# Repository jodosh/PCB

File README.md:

# PCB
eagleCAD files for PCB layouts

Each Directory is an entirly seperate project and should consist of at least 3 files

1)EagleCAD .brd file

2)EagleCAD .sch file

3)README

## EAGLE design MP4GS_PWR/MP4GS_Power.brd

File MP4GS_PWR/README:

This is a board for  the L7808AB 8V regulator input can be 10-35V.
This is used for converting from battery power to the Vin of a Mega2560

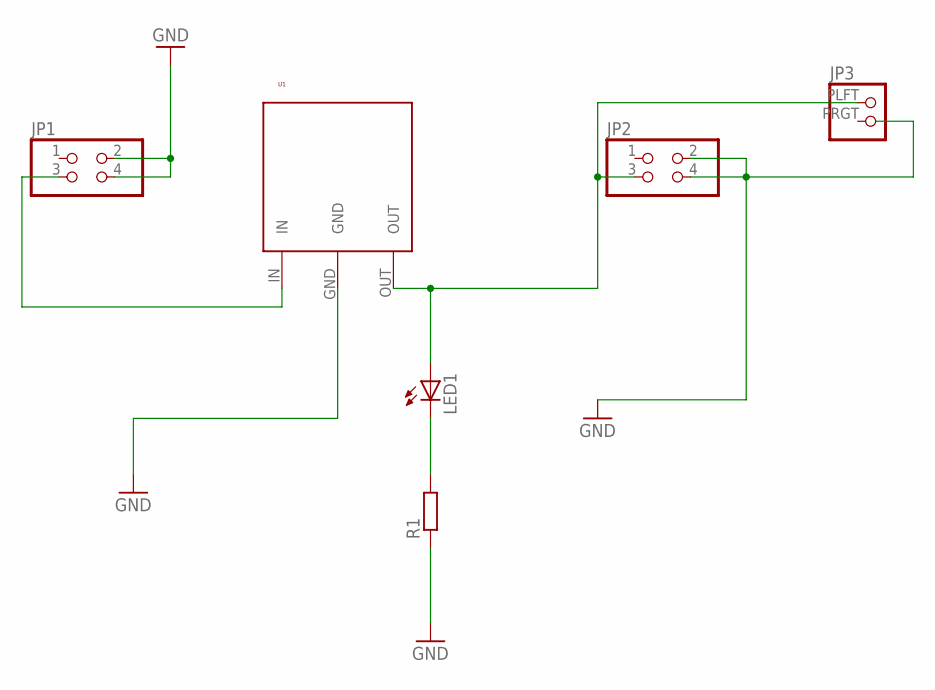
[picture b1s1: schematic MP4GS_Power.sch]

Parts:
JP1, JP2: PINHD-2X2; 2X02
JP3: PINHD-1X2; 1X02
LED1: LED5MM
R1: R-EU_0207/10; 0207/10
U1: L7808AB; L78-DDPAK

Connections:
GND: JP1.2, JP1.4, JP2.2, JP2.4, R1.1, U1.GND
unnamed: JP1.3, U1.IN
unnamed: JP2.3, JP3.PLFT (1), LED1.A, U1.OUT
unnamed: LED1.K (C), R1.2

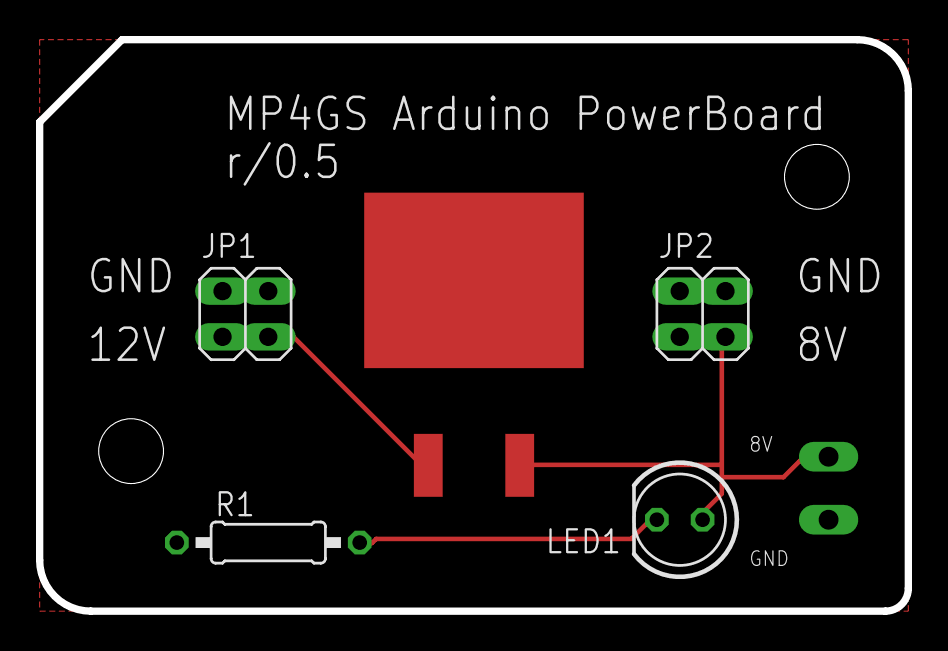
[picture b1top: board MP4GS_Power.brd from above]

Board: 2 copper layers, 48.3 x 31.7 mm, 6 parts (0 on the bottom side), 4 nets.

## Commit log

2015-10-13 Added Shield template for Arduino Mega 2560
2015-10-13 fixed formatting of README.md
2015-11-02 WIP MP4GS_PWR board initial commit
2015-11-03 MP4GS_PWR revisions
    still a WIP
2015-11-03 WIP MP4GS_PWR
2015-11-03 Finalized MP4GS PWR board
2015-11-03 Arduino added ground pours
2015-11-03 Added README for MP4GS_PWR
